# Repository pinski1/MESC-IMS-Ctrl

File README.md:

# MESC IMS Ctrl
A derivative of the Molony ESC. STM32F303 based BLDC logic board designed to interface to an IMS power stage.

Please see https://github.com/davidmolony/MESC_FOC_ESC for further details.

For the most recent schematic check out the 'outputs' folder.

This board is designed to fit on a 12FET power stage IMS PCB

## "MESC_IMS_Ctrl.sch"

* Using STM32F303 like MESC_FOC_ESC
* Using USB 2.0 type C connector for future compatibility
* Using VESC-style connectors for control & hall effect sensors
* Has facility to monitor a thermistor mounted to the power stage PCB
* Can monitor the battery voltage
* Can be powered via USB for configuration on the desk

## "psu.sch"
This sheet contains the power supplies for the ESC. It's designed to accept +40-50V input but won't activate at voltages less than +25V. The LM5-017 is a popular and robust SMPS buck convertor. To minimise supply rail noise but supply the requisite ripple for the feedback circuitry the Texas Instruments application note here: https://www.ti.com/lit/an/snva166a/snva166a.pdf was consulted.

By using a coupled inductor it is possible to get a 2nd, unregulated, output that can be 'stacked' on top of the regulated output. This provides a ~10V supply for the gate drivers. This method of using a coupled inductor to generate a 2nd output is detailed in this Texas Instruments application note here: https://www.ti.com/lit/pdf/snva674.

The +3V3 rail for the microcontroller and current amplifiers comes from a standard SOT23-5 LDO. This minimises noise artefacts and is a simple, low cost, low complexity way of generating this rail.

## "phase.sch"
As this board will plug into the separate power stage PCB it was decided to use isolated gate driver chips. As the gate signals are treated as differential signals this should hopefully allow for fast control while minimising noise, minimising ripple and self-turn-on. The UCC21520 is another well regarded chip. 

The INA240 is used for high speed current sensing, it will take the differential phase current sense signals at the phase voltage and convert them to a single ended current signal with 0A being around 1.65V. There is no additional filtering as this will affect the response of the current amplifier.

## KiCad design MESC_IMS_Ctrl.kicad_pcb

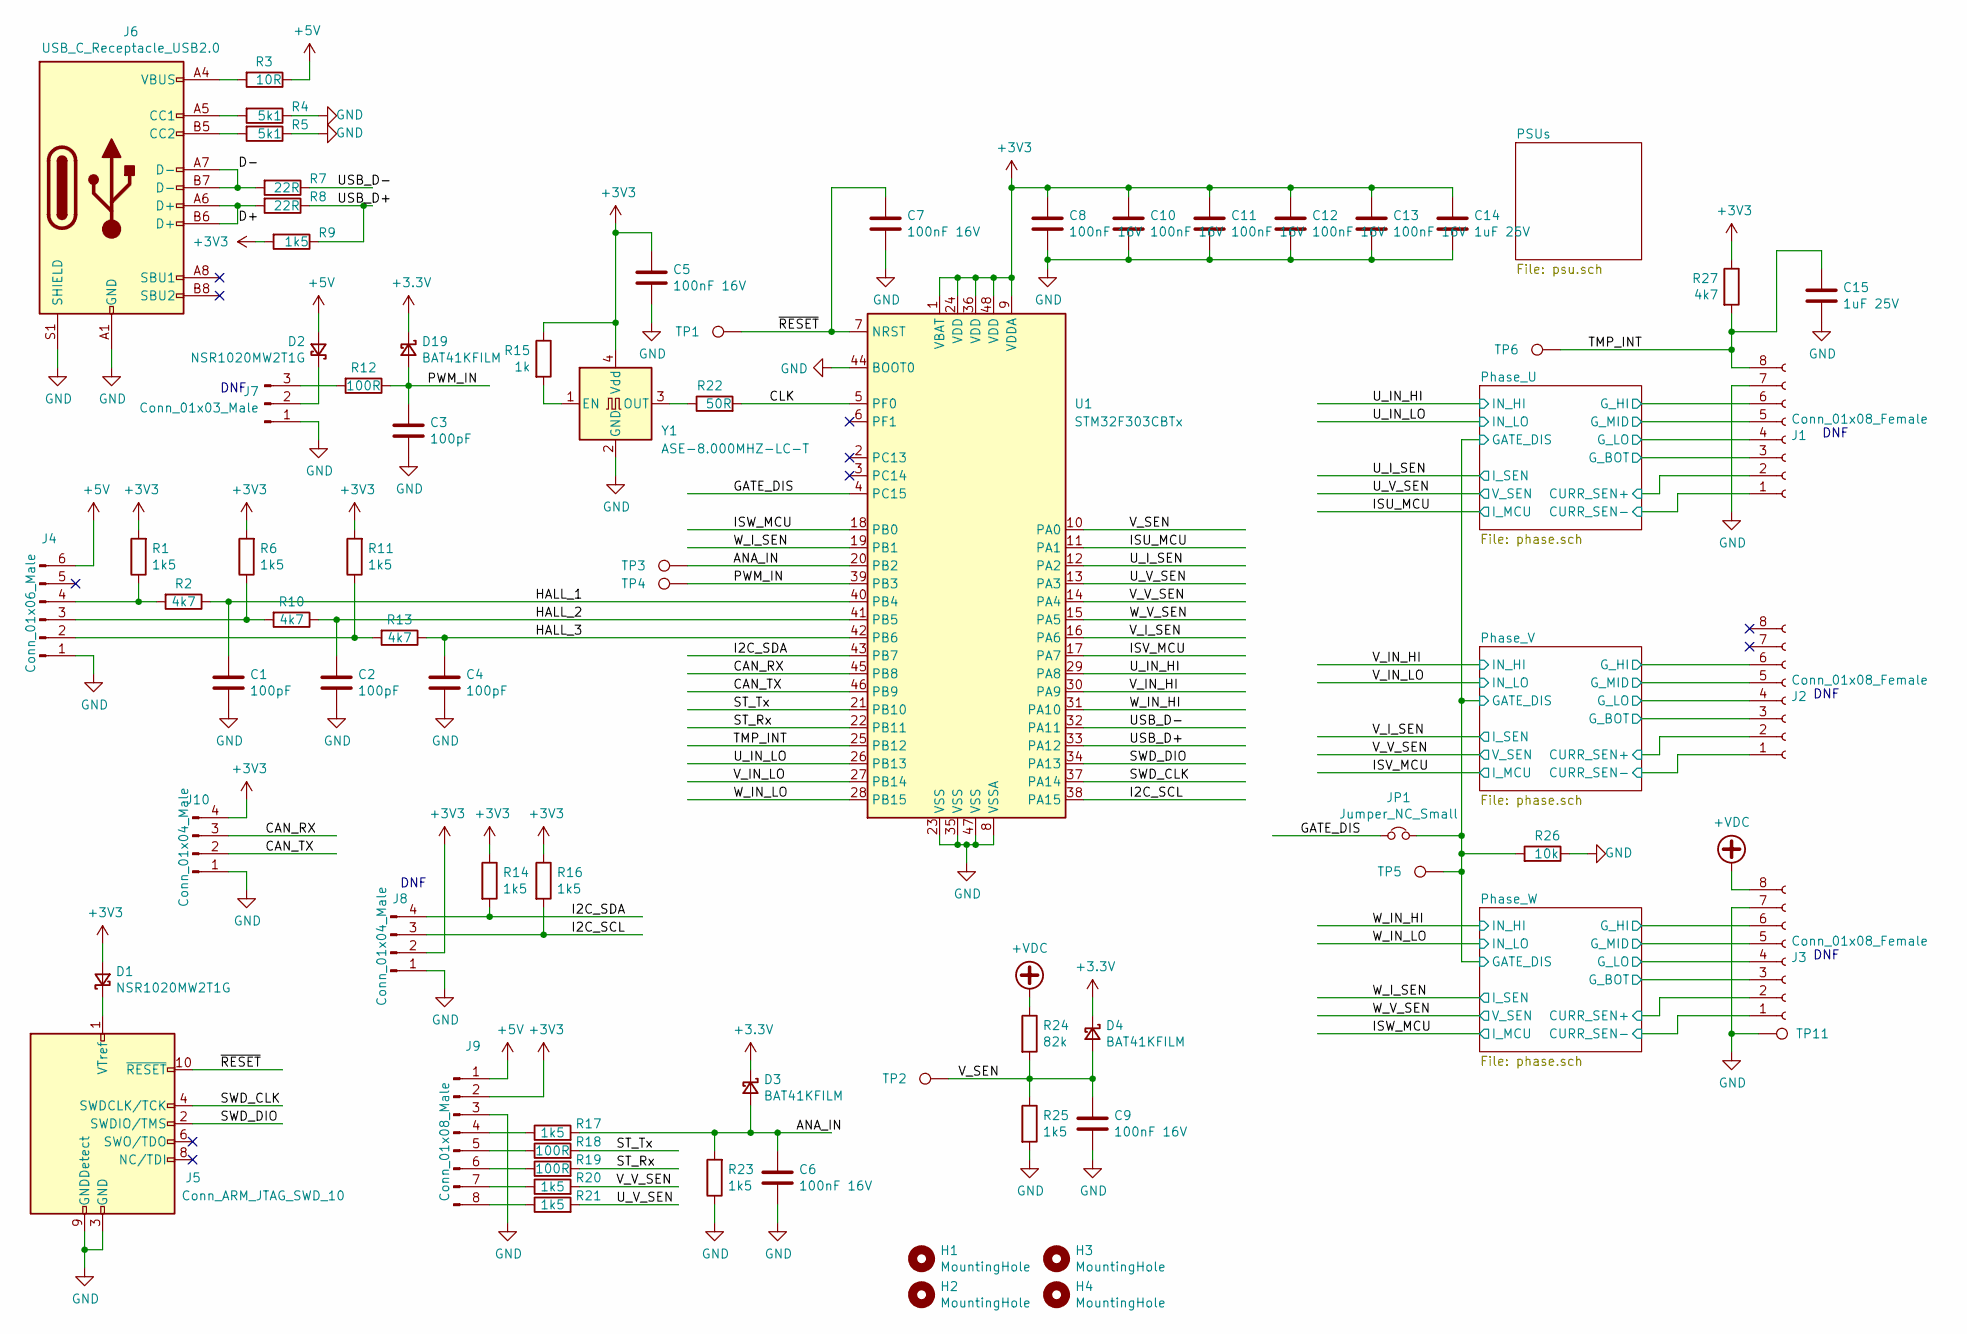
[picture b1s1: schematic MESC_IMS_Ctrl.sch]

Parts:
C1, C2, C3, C4: 100pF; C_0402_1005Metric; LCSC C1546
C5, C6, C7, C8, C9, C10, C11, C12, C13: 100nF 16V; C_0402_1005Metric; LCSC C1525
C14, C15: 1uF 25V; C_0402_1005Metric; LCSC C52923
D1, D2: NSR1020MW2T1G; D_SOD-323; LCSC C116953
D3, D4, D19: BAT41KFILM; D_SOD-523; LCSC C73150
H1, H2, H3, H4: MountingHole; MountingHole_3.2mm_M3_Pad_Via
J1, J2, J3: Conn_01x08_Female; PinSocket_1x08_P2.54mm_Vertical
J4: Conn_01x06_Male; JST_PH_S6B-PH-SM4-TB_1x06-1MP_P2.00mm_Horizontal; LCSC C225237
J5: Conn_ARM_JTAG_SWD_10; PinHeader_2x05_P1.27mm_Vertical; LCSC C239059
J6: USB_C_Receptacle_USB2.0; USB_C_Receptacle_Palconn_UTC16-G; LCSC C165948
J7: Conn_01x03_Male; PinHeader_1x03_P2.54mm_Vertical
J8, J10: Conn_01x04_Male; PinHeader_1x04_P2.54mm_Vertical
J9: Conn_01x08_Male; JST_PH_S8B-PH-SM4-TB_1x08-1MP_P2.00mm_Horizontal; LCSC C225239
JP1: Jumper_NC_Small; SolderJumper-2_P1.3mm_Bridged_RoundedPad1.0x1.5mm
R1, R6, R9, R11, R14, R16, R17, R20, R21, R23: 1k5; R_0402_1005Metric; LCSC C25867
R2, R10, R13, R27: 4k7; R_0402_1005Metric; LCSC C25900
R3: 10R; R_0402_1005Metric; LCSC C25077
R4, R5: 5k1; R_0402_1005Metric; LCSC C25905
R7, R8: 22R; R_0402_1005Metric; LCSC C25092
R12, R18, R19: 100R; R_0402_1005Metric; LCSC C25076
R15: 1k; R_0402_1005Metric; LCSC C11702
R22: 50R; R_0402_1005Metric; LCSC C25120
R24: 82k; R_0603_1608Metric; LCSC C23254
R25: 1k5; R_0603_1608Metric; LCSC C22843
R26: 10k; R_0402_1005Metric; LCSC C25744
TP1, TP2, TP3, TP4, TP5, TP6, TP11: TestPoint; TestPoint_Pad_D1.0mm
U1: STM32F303CBTx; LQFP-48_7x7mm_P0.5mm; LCSC C108516
Y1: ASE-8.000MHZ-LC-T; Oscillator_SMD_Abracon_ASE-4Pin_3.2x2.5mm; LCSC C295522

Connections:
+5V: D2.2 (A), J4.6, J9.1, R3.1; also elsewhere on the board
+VDC: J3.8, R24.1; also elsewhere on the board
/ANA_IN: C6.1, D3.2 (A), R17.2, R23.2, TP3.1, U1.20 (PB2)
/CAN_RX: J10.3, U1.45 (PB8)
/CAN_TX: J10.2, U1.46 (PB9)
/CLK: R22.2, U1.5 (PF0)
/D+: J6.A6 (D+), J6.B6 (D+), R8.2
/D-: J6.A7 (D-), J6.B7 (D-), R7.2
/GATE_DIS: JP1.1, U1.4 (PC15)
/HALL_1: C1.1, R2.1, U1.40 (PB4)
/HALL_2: C2.1, R10.1, U1.41 (PB5)
/HALL_3: C4.1, R13.1, U1.42 (PB6)
/I2C_SCL: J8.3, R16.2, U1.38 (PA15)
/I2C_SDA: J8.4, R14.2, U1.43 (PB7)
/ISU_MCU: U1.11 (PA1); also elsewhere on the board
/ISV_MCU: U1.17 (PA7); also elsewhere on the board
/ISW_MCU: U1.18 (PB0); also elsewhere on the board
/PWM_IN: C3.1, D19.2 (A), R12.1, TP4.1, U1.39 (PB3)
/Phase_U/CURR_SEN+: J1.2; also elsewhere on the board
/Phase_U/CURR_SEN-: J1.1; also elsewhere on the board
/Phase_U/GATE_DIS: JP1.2, R26.2, TP5.1; also elsewhere on the board
/Phase_U/G_BOT: J1.3; also elsewhere on the board
/Phase_U/G_HI: J1.6; also elsewhere on the board
/Phase_U/G_LO: J1.4; also elsewhere on the board
/Phase_U/G_MID: J1.5; also elsewhere on the board
/Phase_V/CURR_SEN+: J2.2; also elsewhere on the board
/Phase_V/CURR_SEN-: J2.1; also elsewhere on the board
/Phase_V/G_BOT: J2.3; also elsewhere on the board
/Phase_V/G_HI: J2.6; also elsewhere on the board
/Phase_V/G_LO: J2.4; also elsewhere on the board
/Phase_V/G_MID: J2.5; also elsewhere on the board
/Phase_W/CURR_SEN+: J3.2; also elsewhere on the board
/Phase_W/CURR_SEN-: J3.1; also elsewhere on the board
/Phase_W/G_BOT: J3.3; also elsewhere on the board
/Phase_W/G_HI: J3.6; also elsewhere on the board
/Phase_W/G_LO: J3.4; also elsewhere on the board
/Phase_W/G_MID: J3.5; also elsewhere on the board
/ST_Rx: R19.2, U1.22 (PB11)
/ST_Tx: R18.2, U1.21 (PB10)
/SWD_CLK: J5.4 (SWDCLK/TCK), U1.37 (PA14)
/SWD_DIO: J5.2 (SWDIO/TMS), U1.34 (PA13)
/TMP_INT: C15.1, J1.8, R27.2, TP6.1, U1.25 (PB12)
/USB_D+: R8.1, R9.1, U1.33 (PA12)
/USB_D-: R7.1, U1.32 (PA11)
/U_IN_HI: U1.29 (PA8); also elsewhere on the board
/U_IN_LO: U1.26 (PB13); also elsewhere on the board
/U_I_SEN: U1.12 (PA2); also elsewhere on the board
/U_V_SEN: R21.2, U1.13 (PA3); also elsewhere on the board
/V_IN_HI: U1.30 (PA9); also elsewhere on the board
/V_IN_LO: U1.27 (PB14); also elsewhere on the board
/V_I_SEN: U1.16 (PA6); also elsewhere on the board
/V_SEN: C9.1, D4.2 (A), R24.2, R25.1, TP2.1, U1.10 (PA0)
/V_V_SEN: R20.2, U1.14 (PA4); also elsewhere on the board
/W_IN_HI: U1.31 (PA10); also elsewhere on the board
/W_IN_LO: U1.28 (PB15); also elsewhere on the board
/W_I_SEN: U1.19 (PB1); also elsewhere on the board
/W_V_SEN: U1.15 (PA5); also elsewhere on the board
/~RESET: C7.1, J5.10 (~RESET~), TP1.1, U1.7 (NRST)
GND: C1.2, C2.2, C3.2, C4.2, C5.2, C6.2, C7.2, C8.2, C9.2, C10.2, C11.2, C12.2, C13.2, C14.2, C15.2, J1.7, J3.7, J4.1, J5.3 (GND), J5.5 (GND), J5.9 (GNDDetect), J6.A1 (GND), J6.A12 (GND), J6.B1 (GND), J6.B12 (GND), J6.S1 (SHIELD), J7.1, J8.1, J9.3, J10.1, R4.1, R5.1, R23.1, R25.2, R26.1, TP11.1, U1.8 (VSSA), U1.23 (VSS), U1.35 (VSS), U1.44 (BOOT0), U1.47 (VSS), Y1.2 (GND); also elsewhere on the board
unnamed: D1.1 (K), J5.1 (VTref)
unnamed: D2.1 (K), J7.2
unnamed: J4.2, R11.1, R13.2
unnamed: J4.3, R6.1, R10.2
unnamed: J4.4, R1.1, R2.2
unnamed: J6.A4 (VBUS), J6.A9 (VBUS), J6.B4 (VBUS), J6.B9 (VBUS), R3.2
unnamed: J6.A5 (CC1), R4.2
unnamed: J6.B5 (CC2), R5.2
unnamed: J7.3, R12.2
unnamed: J9.4, R17.1
unnamed: J9.5, R18.1
unnamed: J9.6, R19.1
unnamed: J9.7, R20.1
unnamed: J9.8, R21.1
unnamed: R15.2, Y1.1 (EN)
unnamed: R22.1, Y1.3 (OUT)

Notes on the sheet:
DNF

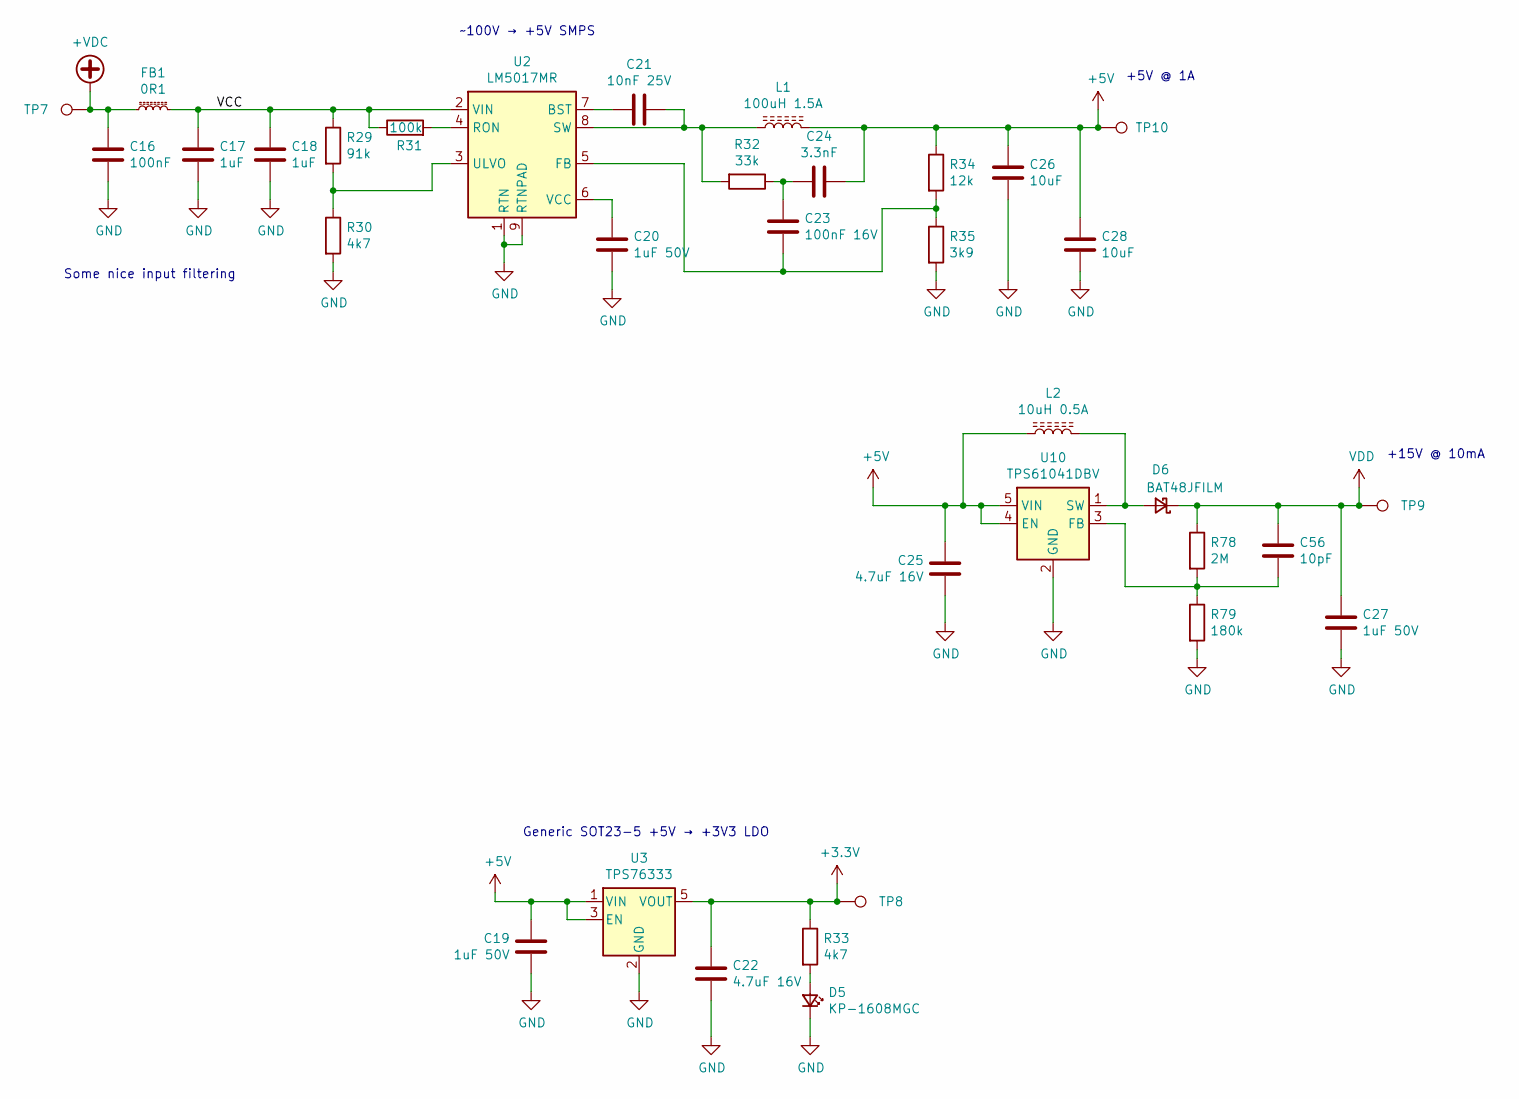
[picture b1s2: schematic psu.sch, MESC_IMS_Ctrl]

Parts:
C16: 100nF; C_0805_2012Metric; LCSC C28233
C17, C18: 1uF; C_1206_3216Metric; LCSC C13832
C19, C20, C27: 1uF 50V; C_0603_1608Metric; LCSC C15849
C21: 10nF 25V; C_0603_1608Metric; LCSC C57112
C22, C25: 4.7uF 16V; C_0603_1608Metric; LCSC C19666
C23: 100nF 16V; C_0402_1005Metric; LCSC C1525
C24: 3.3nF; C_0402_1005Metric; LCSC C26404
C26, C28: 10uF; C_1206_3216Metric; LCSC C13585
C56: 10pF; C_0402_1005Metric; LCSC C32949
D5: KP-1608MGC; D_0603_1608Metric; LCSC C192316
D6: BAT48JFILM; D_SOD-323; LCSC C109204
FB1: 0R1; L_0603_1608Metric; LCSC C80165
L1: 100uH 1.5A; L_Wuerth_HCI-1040; LCSC C497890
L2: 10uH 0.5A; L_0805_2012Metric; LCSC C281113
R29: 91k; R_0603_1608Metric; LCSC C23265
R30: 4k7; R_0603_1608Metric; LCSC C23162
R31: 100k; R_0603_1608Metric; LCSC C25803
R32: 33k; R_0402_1005Metric; LCSC C25779
R33: 4k7; R_0402_1005Metric; LCSC C25900
R34: 12k; R_0402_1005Metric; LCSC C25752
R35: 3k9; R_0402_1005Metric; LCSC C51721
R78: 2M; R_0402_1005Metric; LCSC C11512
R79: 180k; R_0402_1005Metric; LCSC C25760
TP7, TP8, TP9, TP10: TestPoint; TestPoint_Pad_D1.0mm
U2: LM5017MR; SOIC-8-1EP_3.9x4.9mm_P1.27mm_EP2.41x3.3mm; LCSC C34355
U3: TPS76333; SOT-23-5; LCSC C296219
U10: TPS61041DBV; SOT-23-5; LCSC C9846

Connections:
+5V: C19.1, C24.1, C25.1, C26.1, C28.1, L1.2, L2.1, R34.1, TP10.1, U3.1 (VIN), U3.3 (EN), U10.4 (EN), U10.5 (VIN); also elsewhere on the board
+VDC: C16.1, FB1.1, TP7.1; also elsewhere on the board
/PSUs/VCC: C17.1, C18.1, FB1.2, R29.1, R31.1, U2.2 (VIN)
GND: C16.2, C17.2, C18.2, C19.2, C20.2, C22.2, C25.2, C26.2, C27.2, C28.2, D5.1 (K), R30.2, R35.2, R79.2, U2.1 (RTN), U2.9 (RTNPAD), U3.2 (GND), U10.2 (GND); also elsewhere on the board
unnamed: C20.1, U2.6 (VCC)
unnamed: C21.1, L1.1, R32.2, U2.8 (SW)
unnamed: C21.2, U2.7 (BST)
unnamed: C23.1, C24.2, R32.1
unnamed: C23.2, R34.2, R35.1, U2.5 (FB)
unnamed: C56.2, R78.2, R79.1, U10.3 (FB)
unnamed: D5.2 (A), R33.2
unnamed: D6.2 (A), L2.2, U10.1 (SW)
unnamed: R29.2, R30.1, U2.3 (ULVO)
unnamed: R31.2, U2.4 (RON)
VDD: C27.1, C56.1, D6.1 (K), R78.1, TP9.1; also elsewhere on the board

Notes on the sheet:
Generic SOT23-5 +5V → +3V3 LDO
~~100V → +5V SMPS
Some nice input filtering
+15V @ 10mA
+5V @ 1A

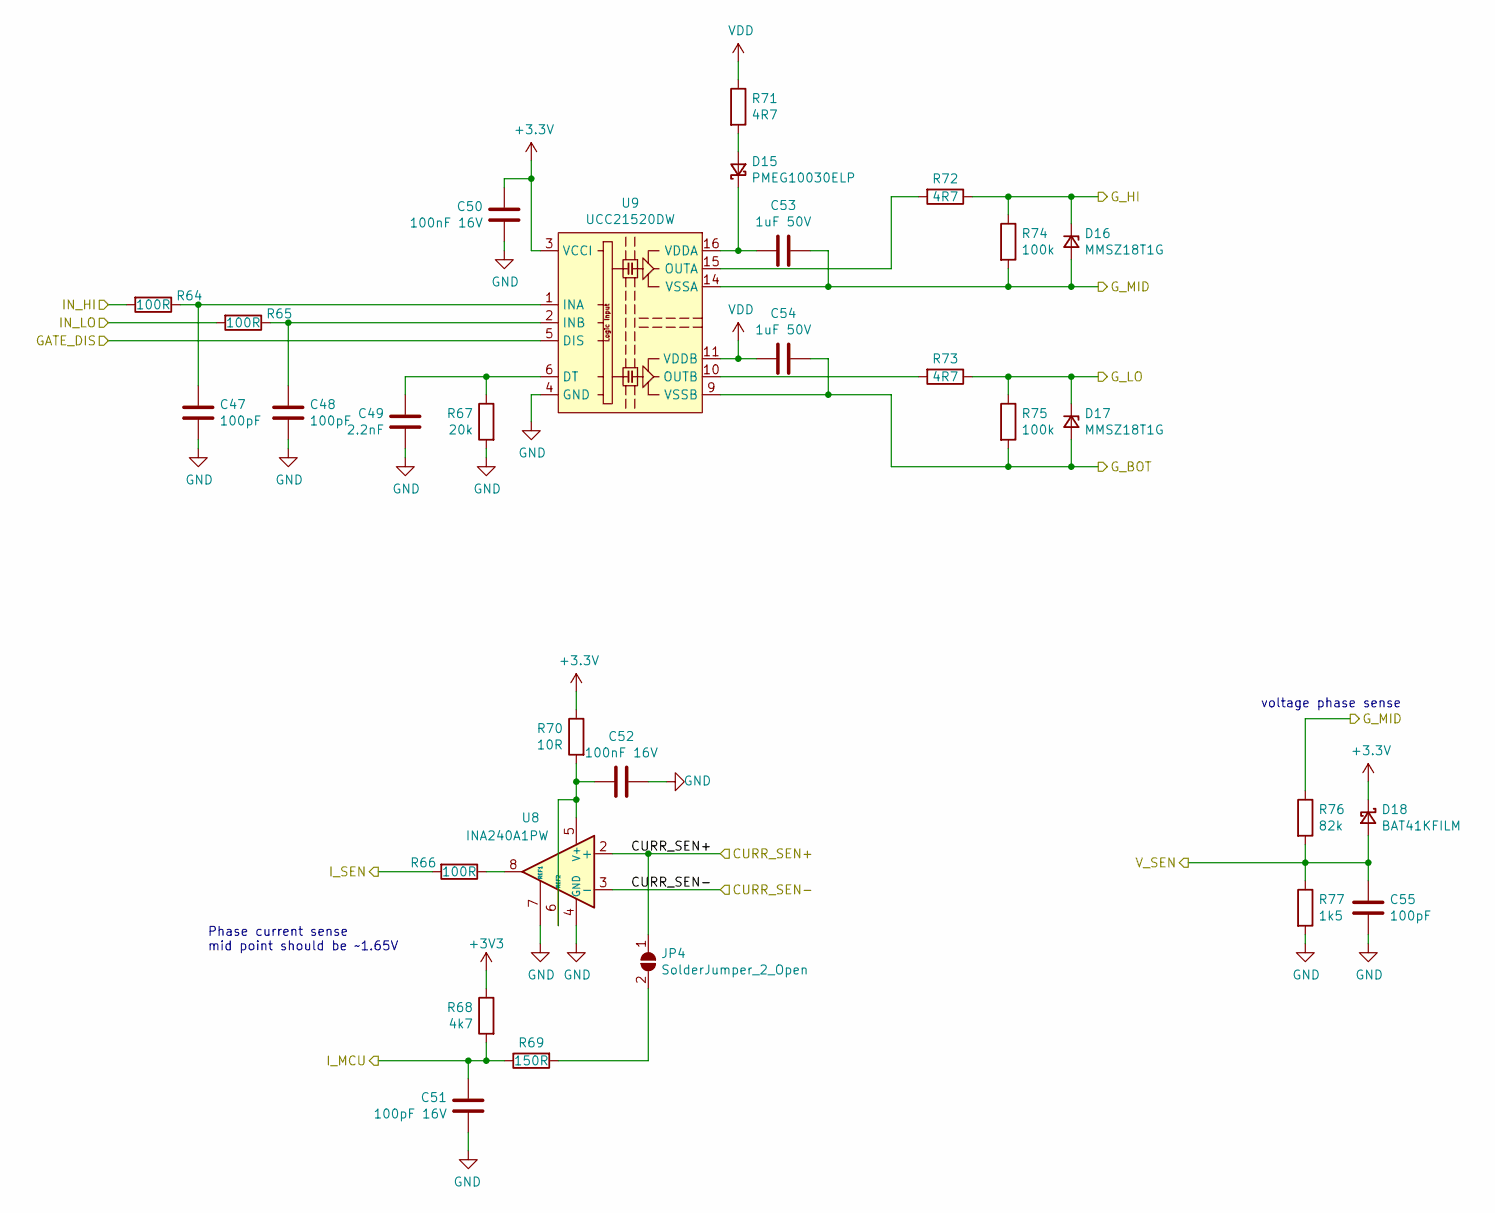
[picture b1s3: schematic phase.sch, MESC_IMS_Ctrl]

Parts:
C29, C30, C37: 100pF; C_0402_1005Metric; LCSC C1546
C31: 2.2nF; C_0603_1608Metric; LCSC C1604
C32, C34: 100nF 16V; C_0402_1005Metric; LCSC C1525
C33: 100pF 16V; C_0402_1005Metric; LCSC C1546
C35, C36: 1uF 50V; C_0603_1608Metric; LCSC C15849
D7: PMEG10030ELP; D_SOD-128; LCSC C503376
D8, D9: MMSZ18T1G; D_SOD-123; LCSC C382948
D10: BAT41KFILM; D_SOD-523; LCSC C73150
JP2: SolderJumper_2_Open; SolderJumper-2_P1.3mm_Open_RoundedPad1.0x1.5mm
R36, R37, R38: 100R; R_0402_1005Metric; LCSC C25076
R39: 20k; R_0603_1608Metric; LCSC C4184
R40: 4k7; R_0402_1005Metric; LCSC C25900
R41: 150R; R_0402_1005Metric; LCSC C25082
R42: 10R; R_0402_1005Metric; LCSC C25077
R43, R44, R45: 4R7; R_0805_2012Metric; LCSC C17675
R46, R47: 100k; R_0402_1005Metric; LCSC C25741
R48: 82k; R_0603_1608Metric; LCSC C23254
R49: 1k5; R_0603_1608Metric; LCSC C22843
U4: INA240A1PW; TSSOP-8_4.4x3mm_P0.65mm; LCSC C129949
U5: UCC21520DW; SOIC-16W_7.5x10.3mm_P1.27mm; LCSC C189707

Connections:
/ISU_MCU: C33.1, R40.2, R41.1; also elsewhere on the board
/Phase_U/CURR_SEN+: JP2.1 (A), U4.2 (+); also elsewhere on the board
/Phase_U/CURR_SEN-: U4.3 (-); also elsewhere on the board
/Phase_U/GATE_DIS: U5.5 (DIS); also elsewhere on the board
/Phase_U/G_BOT: C36.1, D9.2 (A), R47.2, U5.9 (VSSB); also elsewhere on the board
/Phase_U/G_HI: D8.1 (K), R44.1, R46.1; also elsewhere on the board
/Phase_U/G_LO: D9.1 (K), R45.1, R47.1; also elsewhere on the board
/Phase_U/G_MID: C35.1, D8.2 (A), R46.2, R48.1, U5.14 (VSSA); also elsewhere on the board
/U_IN_HI: R36.2; also elsewhere on the board
/U_IN_LO: R37.2; also elsewhere on the board
/U_I_SEN: R38.2; also elsewhere on the board
/U_V_SEN: C37.1, D10.2 (A), R48.2, R49.1; also elsewhere on the board
GND: C29.2, C30.2, C31.1, C32.2, C33.2, C34.1, C37.2, R39.2, R49.2, U4.1 (GND), U4.4 (GND), U4.7 (REF1), U5.4 (GND); also elsewhere on the board
unnamed: C29.1, R36.1, U5.1 (INA)
unnamed: C30.1, R37.1, U5.2 (INB)
unnamed: C31.2, R39.1, U5.6 (DT)
unnamed: C34.2, R42.2, U4.5 (V+), U4.6 (REF2)
unnamed: C35.2, D7.1 (K), U5.16 (VDDA)
unnamed: D7.2 (A), R43.2
unnamed: JP2.2 (B), R41.2
unnamed: R38.1, U4.8
unnamed: R44.2, U5.15 (OUTA)
unnamed: R45.2, U5.10 (OUTB)
VDD: C36.2, R43.1, U5.11 (VDDB); also elsewhere on the board

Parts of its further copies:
C38, C39, C46, C47, C48, C55: 100pF; C_0402_1005Metric; LCSC C1546
C40, C49: 2.2nF; C_0603_1608Metric; LCSC C1604
C41, C43, C50, C52: 100nF 16V; C_0402_1005Metric; LCSC C1525
C42, C51: 100pF 16V; C_0402_1005Metric; LCSC C1546
C44, C45, C53, C54: 1uF 50V; C_0603_1608Metric; LCSC C15849
D11, D15: PMEG10030ELP; D_SOD-128; LCSC C503376
D12, D13, D16, D17: MMSZ18T1G; D_SOD-123; LCSC C382948
D14, D18: BAT41KFILM; D_SOD-523; LCSC C73150
JP3, JP4: SolderJumper_2_Open; SolderJumper-2_P1.3mm_Open_RoundedPad1.0x1.5mm
R50, R51, R52, R64, R65, R66: 100R; R_0402_1005Metric; LCSC C25076
R53, R67: 20k; R_0603_1608Metric; LCSC C4184
R54, R68: 4k7; R_0402_1005Metric; LCSC C25900
R55, R69: 150R; R_0402_1005Metric; LCSC C25082
R56, R70: 10R; R_0402_1005Metric; LCSC C25077
R57, R58, R59, R71, R72, R73: 4R7; R_0805_2012Metric; LCSC C17675
R60, R61, R74, R75: 100k; R_0402_1005Metric; LCSC C25741
R62, R76: 82k; R_0603_1608Metric; LCSC C23254
R63, R77: 1k5; R_0603_1608Metric; LCSC C22843
U6, U8: INA240A1PW; TSSOP-8_4.4x3mm_P0.65mm; LCSC C129949
U7, U9: UCC21520DW; SOIC-16W_7.5x10.3mm_P1.27mm; LCSC C189707

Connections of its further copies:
/ISV_MCU: C42.1, R54.2, R55.1; also elsewhere on the board
/ISW_MCU: C51.1, R68.2, R69.1; also elsewhere on the board
/Phase_U/GATE_DIS: U7.5 (DIS), U9.5 (DIS); also elsewhere on the board
/Phase_V/CURR_SEN+: JP3.1 (A), U6.2 (+); also elsewhere on the board
/Phase_V/CURR_SEN-: U6.3 (-); also elsewhere on the board
/Phase_V/G_BOT: C45.1, D13.2 (A), R61.2, U7.9 (VSSB); also elsewhere on the board
/Phase_V/G_HI: D12.1 (K), R58.1, R60.1; also elsewhere on the board
/Phase_V/G_LO: D13.1 (K), R59.1, R61.1; also elsewhere on the board
/Phase_V/G_MID: C44.1, D12.2 (A), R60.2, R62.1, U7.14 (VSSA); also elsewhere on the board
/Phase_W/CURR_SEN+: JP4.1 (A), U8.2 (+); also elsewhere on the board
/Phase_W/CURR_SEN-: U8.3 (-); also elsewhere on the board
/Phase_W/G_BOT: C54.1, D17.2 (A), R75.2, U9.9 (VSSB); also elsewhere on the board
/Phase_W/G_HI: D16.1 (K), R72.1, R74.1; also elsewhere on the board
/Phase_W/G_LO: D17.1 (K), R73.1, R75.1; also elsewhere on the board
/Phase_W/G_MID: C53.1, D16.2 (A), R74.2, R76.1, U9.14 (VSSA); also elsewhere on the board
/V_IN_HI: R50.2; also elsewhere on the board
/V_IN_LO: R51.2; also elsewhere on the board
/V_I_SEN: R52.2; also elsewhere on the board
/V_V_SEN: C46.1, D14.2 (A), R62.2, R63.1; also elsewhere on the board
/W_IN_HI: R64.2; also elsewhere on the board
/W_IN_LO: R65.2; also elsewhere on the board
/W_I_SEN: R66.2; also elsewhere on the board
/W_V_SEN: C55.1, D18.2 (A), R76.2, R77.1; also elsewhere on the board
GND: C38.2, C39.2, C40.1, C41.2, C42.2, C43.1, C46.2, C47.2, C48.2, C49.1, C50.2, C51.2, C52.1, C55.2, R53.2, R63.2, R67.2, R77.2, U6.1 (GND), U6.4 (GND), U6.7 (REF1), U7.4 (GND), U8.1 (GND), U8.4 (GND), U8.7 (REF1), U9.4 (GND); also elsewhere on the board
unnamed: C38.1, R50.1, U7.1 (INA)
unnamed: C39.1, R51.1, U7.2 (INB)
unnamed: C40.2, R53.1, U7.6 (DT)
unnamed: C43.2, R56.2, U6.5 (V+), U6.6 (REF2)
unnamed: C44.2, D11.1 (K), U7.16 (VDDA)
unnamed: C47.1, R64.1, U9.1 (INA)
unnamed: C48.1, R65.1, U9.2 (INB)
unnamed: C49.2, R67.1, U9.6 (DT)
unnamed: C52.2, R70.2, U8.5 (V+), U8.6 (REF2)
unnamed: C53.2, D15.1 (K), U9.16 (VDDA)
unnamed: D11.2 (A), R57.2
unnamed: D15.2 (A), R71.2
unnamed: JP3.2 (B), R55.2
unnamed: JP4.2 (B), R69.2
unnamed: R52.1, U6.8
unnamed: R58.2, U7.15 (OUTA)
unnamed: R59.2, U7.10 (OUTB)
unnamed: R66.1, U8.8
unnamed: R72.2, U9.15 (OUTA)
unnamed: R73.2, U9.10 (OUTB)
VDD: C45.2, C54.2, R57.1, R71.1, U7.11 (VDDB), U9.11 (VDDB); also elsewhere on the board

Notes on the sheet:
Phase current sense mid point should be ~~1.65V
voltage phase sense

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
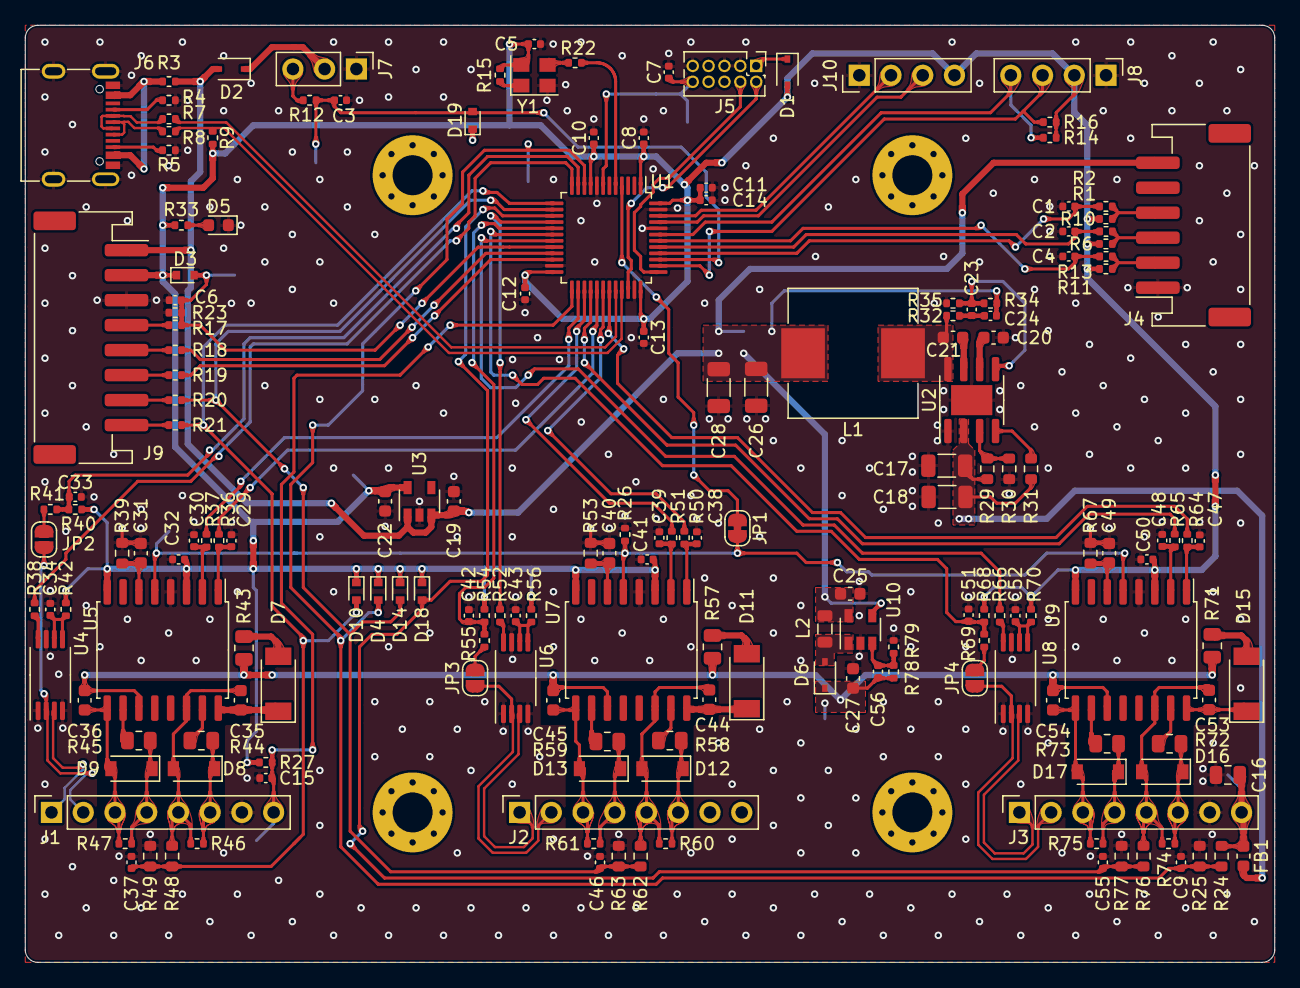
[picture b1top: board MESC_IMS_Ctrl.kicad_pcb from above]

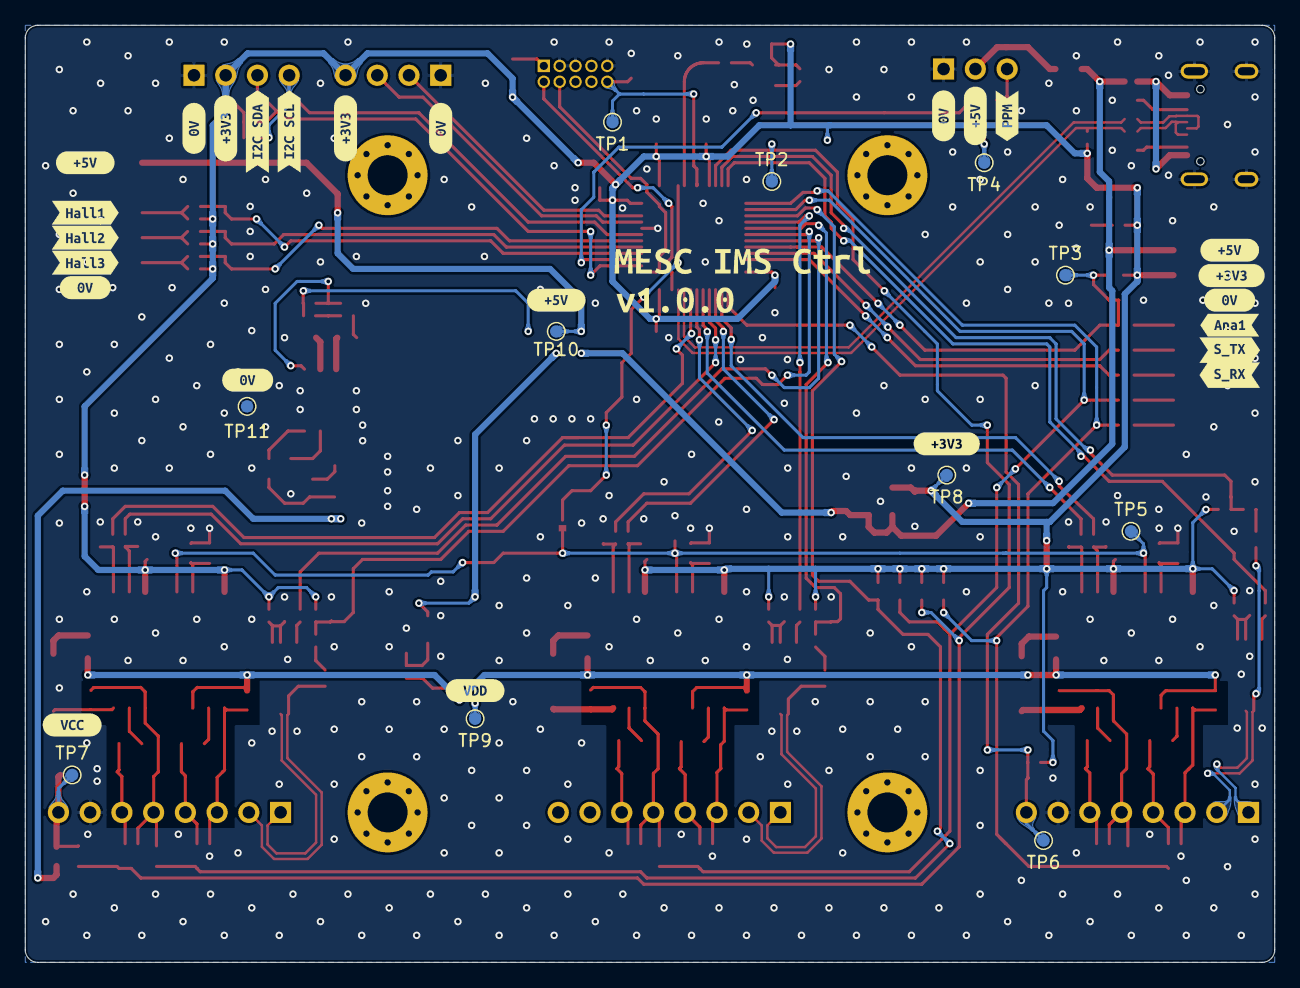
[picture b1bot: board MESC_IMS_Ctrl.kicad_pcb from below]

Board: 4 copper layers, 100.0 x 75.0 mm, 223 parts (38 on the bottom side), 118 nets.

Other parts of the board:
svg2mod, svg2mod#2, svg2mod#3, svg2mod#4, svg2mod#5, svg2mod#6, svg2mod#7, svg2mod#8, svg2mod#9, svg2mod#10, svg2mod#11, svg2mod#12, svg2mod#13, svg2mod#14, svg2mod#15, svg2mod#16, svg2mod#17, svg2mod#18, svg2mod#19, svg2mod#20, svg2mod#21, svg2mod#22, svg2mod#23: G***; label
svgemod: G***; label
svgemod#2, svgemod#3, svgemod#4: G***; label

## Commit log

2021-04-10 Adding the initial files
2021-04-10 Minor updates
    Tweaking the README.md
    Removing F303 op-amp circuitry.
    Re-arranging INA240 circuit
2021-04-10 Adding some test points
2021-04-10 Tarting up the README.md
2021-04-11 Assigned all footprints
    Began initial placement
2021-04-11 Small mistake with git ignore
2021-04-11 Minor name change
2021-04-11 Adding low-side current comparators
2021-04-12 Adding LCSC part numbers
2021-04-19 Twaeking the layout to fit into 100x100mm
2021-04-19 More placement
2021-04-19 Adding some basic test tracks
2021-04-19 Cleaned up the schematic
    Also regenerated the pdf & set boot diodes to SOD128.
2021-04-20 Initial gate driver placement/routing
    Also adding images to README
2021-04-20 README.md churn
2021-04-20 Fixed images in README.md
2021-04-25 Continuing routing
2021-04-25 Some more routing
2021-04-26 moved crystal, made curr sense regular
2021-04-28 Tweaked LM5017 package
2021-04-28 Removed coupled inductor
    Added TPS61041DB
2021-04-29 Playing with pours
2021-05-01 Some minor tweaks
2021-05-05 Tweaking potential dividers
2021-05-06 Routing 3V3 reg
2021-05-06 More routing
2021-05-08 Routing nearly complete
    some diodes made smaller
2021-05-08 Adding via stitching and teardrops
2021-05-09 Updated part numbers
2021-05-09 Adding 0V TP and labels
2021-05-09 upgrading to 4layer
